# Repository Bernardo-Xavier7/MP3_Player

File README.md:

# Description
Just a simple MP3 player project. Features a built-in microphone, Wifi and Bluetooth, internal flash and SD card support and two audio ports.

# To-Do
- [ ] Hardware
  - [x] Schematic
    - [x] MCU
    - [x] USB
    - [x] Power
    - [x] Audio
    - [x] Storage
    - [x] Buttons
    - [x] Display
    - [x] Wireless
    - [x] Revision
    - [x] BOM
    - [x] Footprint Assignment
  - [ ] PCB
    - [x] Layout
    - [x] Routing
    - [x] Revision
  - [ ] Firmware
    - [ ] Menu
      - [ ] Buttons
      - [ ] Display
    - [ ] USB Handling
    - [ ] Power Measuring and Display
    - [ ] Play Audio
    - [ ] Record
    - [ ] SD Card File System and Mass Storage
    - [ ] Wireless Conectivity
    - [ ] Revision
  - [ ] Case
    - [ ] Model
    - [ ] Test
    - [ ] Revision
# Useful Links
| Link | Description |
| ---- | ---- |
| https://snapeda.com | Symbols/Footprints/3DModels |
| https://octopart.com | Multi-seller component browser |
| https://buydisplay.com | Display shop |
| https://panelook.com | Display shop |
| [https://dev.st.com](https://dev.st.com/stm32cube-docs/stm32cube-getting-started/1.1.1/en/markup/Ecosystem_Select/Ecosystem_Select_MCU_Board.html) | STM32 development guide |

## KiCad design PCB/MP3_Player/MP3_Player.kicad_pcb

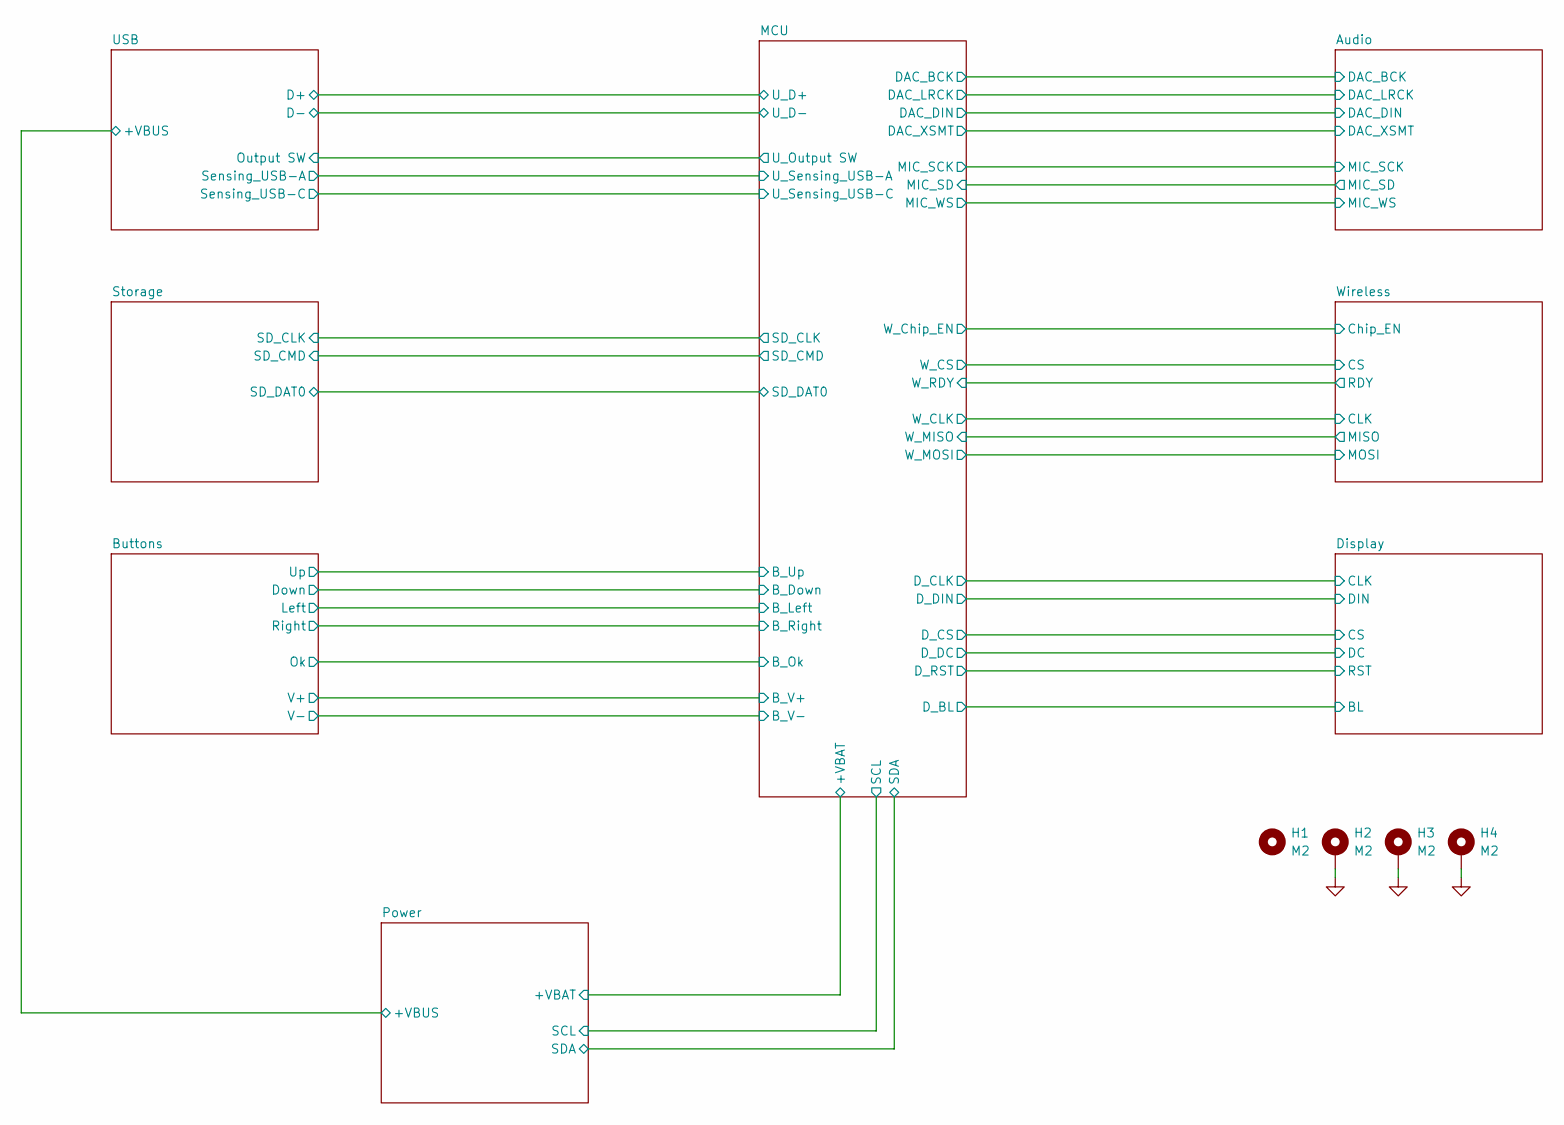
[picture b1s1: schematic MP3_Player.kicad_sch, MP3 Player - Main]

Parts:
H1: M2; MountingHole_2.2mm_M2
H2, H3, H4: M2; MountingHole_2.2mm_M2_DIN965_Pad_TopBottom

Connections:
GND: H2.1 (1_1), H3.1 (1_1), H4.1 (1_1); also elsewhere on the board

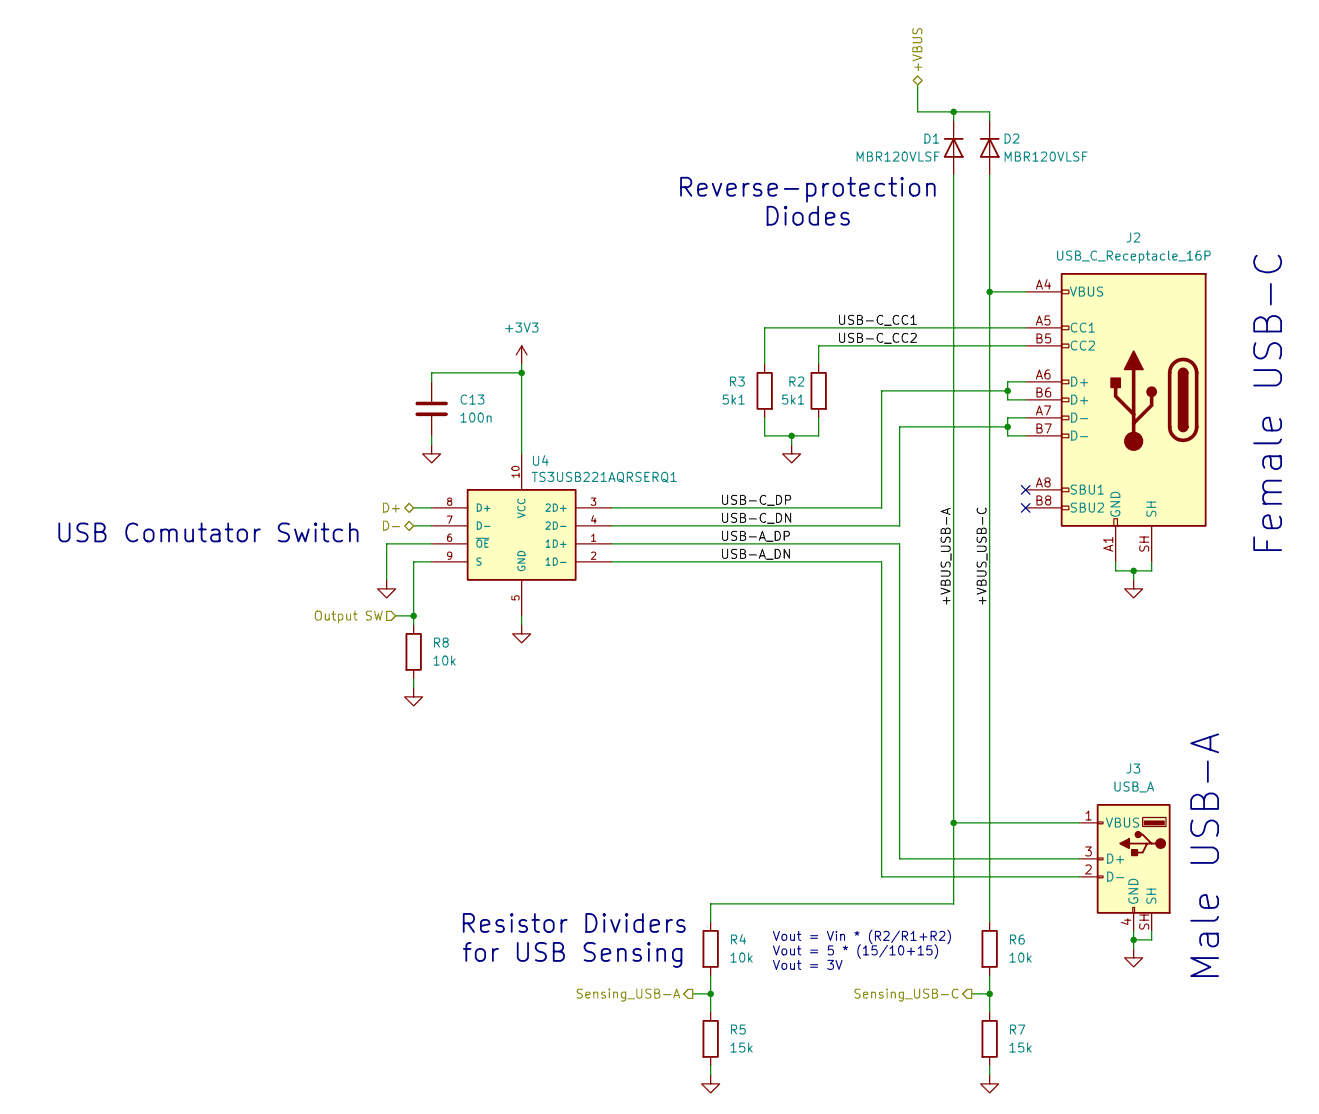
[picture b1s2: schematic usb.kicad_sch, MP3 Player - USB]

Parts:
C13: 100n; C_0402_1005Metric; Mfr. Part # CL05B104KP5NNNC
D1, D2: MBR120VLSF; D_SOD-123F; Mfr. Part # MBR120VLSFT3G
J2: USB_C_Receptacle_16P; USB_C_Receptacle_G-Switch_GT-USB-7010ASV; Mfr. Part # UJ20-C-H-C-4-SMT-TR
J3: USB_A; USB_A_CNCTech_1001-011-01101_Horizontal; Mfr. Part # 931
R2, R3: 5k1; R_0402_1005Metric; Mfr. Part # CRCW04025K10FKED
R4, R6, R8: 10k; R_0402_1005Metric; Mfr. Part # CRCW040210K0FKED
R5, R7: 15k; R_0402_1005Metric; Mfr. Part # CRCW040215K0FKED
U4: TS3USB221AQRSERQ1; MOUSER_PART_NUMBER 595-S3USB221AQRSERQ1

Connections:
+3V3: C13.1, U4.10 (VCC); also elsewhere on the board
/MCU/U_D+: U4.8 (D+); also elsewhere on the board
/MCU/U_D-: U4.7 (D-); also elsewhere on the board
/MCU/U_Output SW: R8.1, U4.9 (S); also elsewhere on the board
/MCU/U_Sensing_USB-A: R4.2, R5.1; also elsewhere on the board
/MCU/U_Sensing_USB-C: R6.2, R7.1; also elsewhere on the board
/Power/+VBUS: D1.1 (K), D2.1 (K); also elsewhere on the board
/USB/+VBUS_USB-A: D1.2 (A), J3.1 (VBUS), R4.1
/USB/+VBUS_USB-C: D2.2 (A), J2.A4 (VBUS), J2.A9 (VBUS), J2.B4 (VBUS), J2.B9 (VBUS), R6.1
/USB/USB-A_DN: J3.2 (D-), U4.2 (1D-)
/USB/USB-A_DP: J3.3 (D+), U4.1 (1D+)
/USB/USB-C_CC1: J2.A5 (CC1), R3.1
/USB/USB-C_CC2: J2.B5 (CC2), R2.1
/USB/USB-C_DN: J2.A7 (D-), J2.B7 (D-), U4.4 (2D-)
/USB/USB-C_DP: J2.A6 (D+), J2.B6 (D+), U4.3 (2D+)
GND: C13.2, J2.A1 (GND), J2.A12 (GND), J2.B1 (GND), J2.B12 (GND), J2.SH, J3.4 (GND), J3.SH, R2.2, R3.2, R5.2, R7.2, R8.2, U4.5 (GND), U4.6 (~OE); also elsewhere on the board

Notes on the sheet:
Vout = Vin * (R2/R1+R2) Vout = 5 * (15/10+15) Vout = 3V
Reverse-protection Diodes
USB Comutator Switch
Male USB-A
Resistor Dividers for USB Sensing
Female USB-C

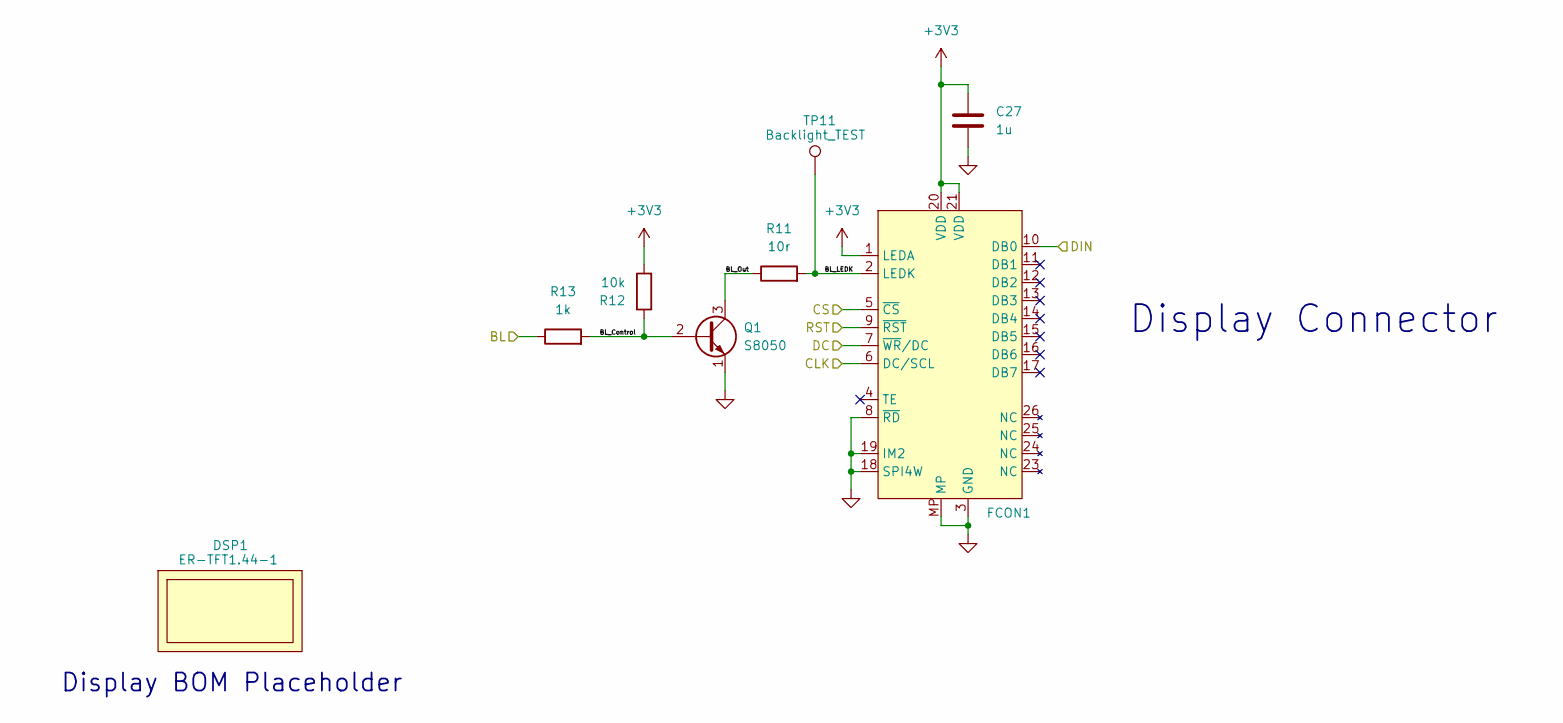
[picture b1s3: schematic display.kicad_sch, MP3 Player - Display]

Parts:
C27: 1u; C_0402_1005Metric; Mfr. Part # CL05A105MQ5NNND
DSP1: ER-TFT1.44-1; N/A; Mfr. Part # ER-TFT1.44-1
FCON1: 26 Pins 0.5mm; Amphenol_F32R-1A7x1-11026_1x26-1MP_P0.5mm_Horizontal
Q1: S8050; TSOT-23; Mfr. Part # S8050
R11: 10r; R_0603_1608Metric; Mfr. Part # CRCW060310R0FKEA
R12: 10k; R_0402_1005Metric; Mfr. Part # CRCW040210K0FKED
R13: 1k; R_0402_1005Metric; Mfr. Part # CRCW04021K00FKED
TP11: Backlight_TEST; TestPoint_Pad_D1.0mm

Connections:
+3V3: C27.1, FCON1.1 (LEDA), FCON1.20 (VDD), FCON1.21 (VDD), R12.2; also elsewhere on the board
/Display/BL: R13.1; also elsewhere on the board
/Display/BL_Control: Q1.2 (B), R12.1, R13.2
/Display/BL_LEDK: FCON1.2 (LEDK), R11.2, TP11.1 (1_1)
/Display/BL_Out: Q1.3 (C), R11.1
/Display/CLK: FCON1.6 (DC/SCL); also elsewhere on the board
/Display/CS: FCON1.5 (~CS); also elsewhere on the board
/Display/DC: FCON1.7 (~WR/DC); also elsewhere on the board
/Display/DIN: FCON1.10 (DB0); also elsewhere on the board
/Display/RST: FCON1.9 (~RST); also elsewhere on the board
GND: C27.2, FCON1.3 (GND), FCON1.8 (~RD), FCON1.18 (SPI4W), FCON1.19 (IM2), FCON1.22 (GND), FCON1.MP, Q1.1 (E); also elsewhere on the board

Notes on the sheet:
Display BOM Placeholder
Display Connector

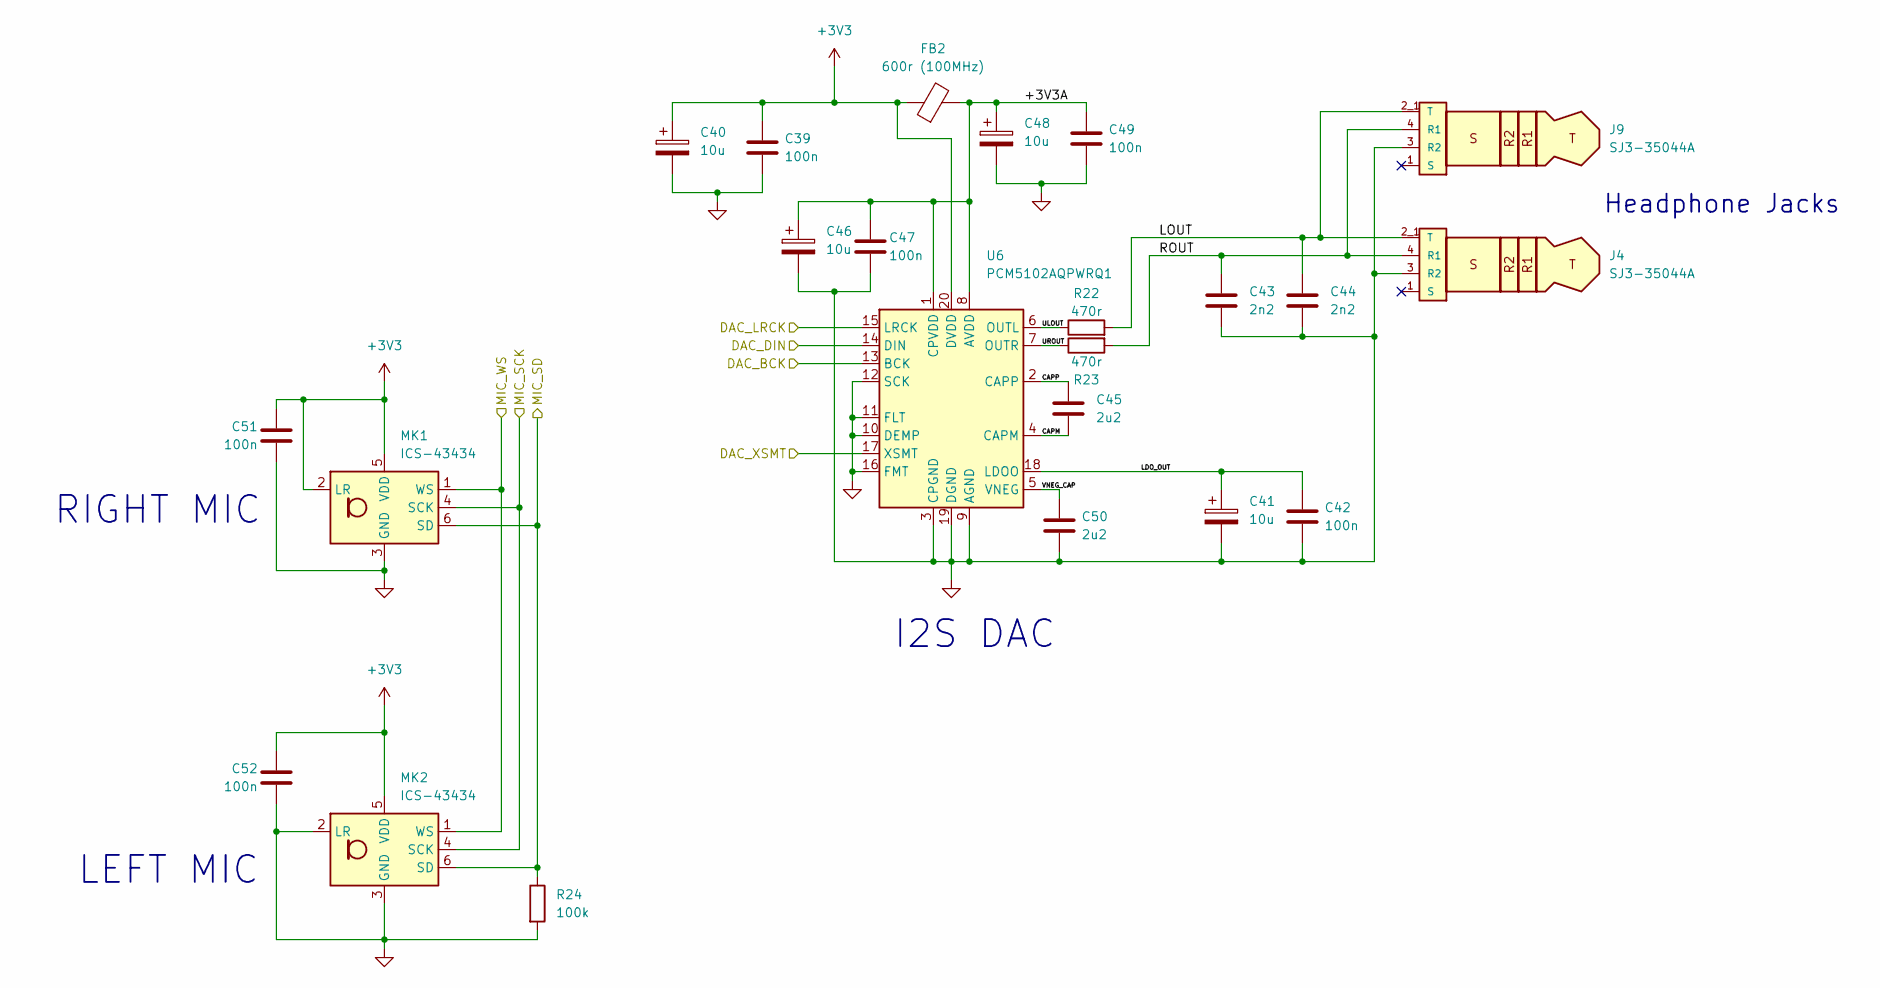
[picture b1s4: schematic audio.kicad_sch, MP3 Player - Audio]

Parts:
C39, C42, C47, C49, C51, C52: 100n; C_0402_1005Metric; Mfr. Part # CL05B104KP5NNNC
C40, C41, C46, C48: 10u; CP_EIA-2012-15_AVX-P; Mfr. Part # T529P106M010AAE200
C43, C44: 2n2; C_0402_1005Metric; Mfr. Part # CL05B222JB5NNNC
C45, C50: 2u2; C_0402_1005Metric; Mfr. Part # CL05A225MQ5NNND
FB2: 600r (100MHz); C_0402_1005Metric; Mfr. Part # BLM15AG601SN1D
J4, J9: SJ3-35044A; SAMESKY_SJ3-35044A; PARTREV 1.0
MK1, MK2: ICS-43434; InvenSense_ICS-43434-6_3.5x2.65mm; Mfr. Part # ICS-43434
R22, R23: 470r; R_0603_1608Metric; Mfr. Part # CRCW0603470RFKEA
R24: 100k; R_0402_1005Metric; Mfr. Part # CRCW0402100KFKED
U6: PCM5102AQPWRQ1; TSSOP-20_4.4x6.5mm_P0.65mm; Mfr. Part # PCM5102AQPWRQ1

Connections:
+3V3: C39.1, C40.1, C51.1, C52.1, FB2.1, MK1.2 (LR), MK1.5 (VDD), MK2.5 (VDD), U6.20 (DVDD); also elsewhere on the board
/Audio/+3V3A: C46.1, C47.1, C48.1, C49.1, FB2.2, U6.1 (CPVDD), U6.8 (AVDD)
/Audio/CAPM: C45.2, U6.4 (CAPM)
/Audio/CAPP: C45.1, U6.2 (CAPP)
/Audio/DAC_BCK: U6.13 (BCK); also elsewhere on the board
/Audio/DAC_DIN: U6.14 (DIN); also elsewhere on the board
/Audio/DAC_LRCK: U6.15 (LRCK); also elsewhere on the board
/Audio/DAC_XSMT: U6.17 (XSMT); also elsewhere on the board
/Audio/LDO_OUT: C41.1, C42.1, U6.18 (LDOO)
/Audio/LOUT: C44.1, J4.2_1 (T), J4.2_2, J9.2_1 (T), J9.2_2, R22.2
/Audio/MIC_SCK: MK1.4 (SCK), MK2.4 (SCK); also elsewhere on the board
/Audio/MIC_SD: MK1.6 (SD), MK2.6 (SD), R24.1; also elsewhere on the board
/Audio/MIC_WS: MK1.1 (WS), MK2.1 (WS); also elsewhere on the board
/Audio/ROUT: C43.1, J4.4 (R1), J9.4 (R1), R23.2
/Audio/ULOUT: R22.1, U6.6 (OUTL)
/Audio/UROUT: R23.1, U6.7 (OUTR)
/Audio/VNEG_CAP: C50.1, U6.5 (VNEG)
GND: C39.2, C40.2, C41.2, C42.2, C43.2, C44.2, C46.2, C47.2, C48.2, C49.2, C50.2, C51.2, C52.2, J4.3 (R2), J9.3 (R2), MK1.3 (GND), MK2.2 (LR), MK2.3 (GND), R24.2, U6.3 (CPGND), U6.9 (AGND), U6.10 (DEMP), U6.11 (FLT), U6.12 (SCK), U6.16 (FMT), U6.19 (DGND); also elsewhere on the board

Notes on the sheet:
Headphone Jacks
LEFT MIC
I2S DAC
RIGHT MIC

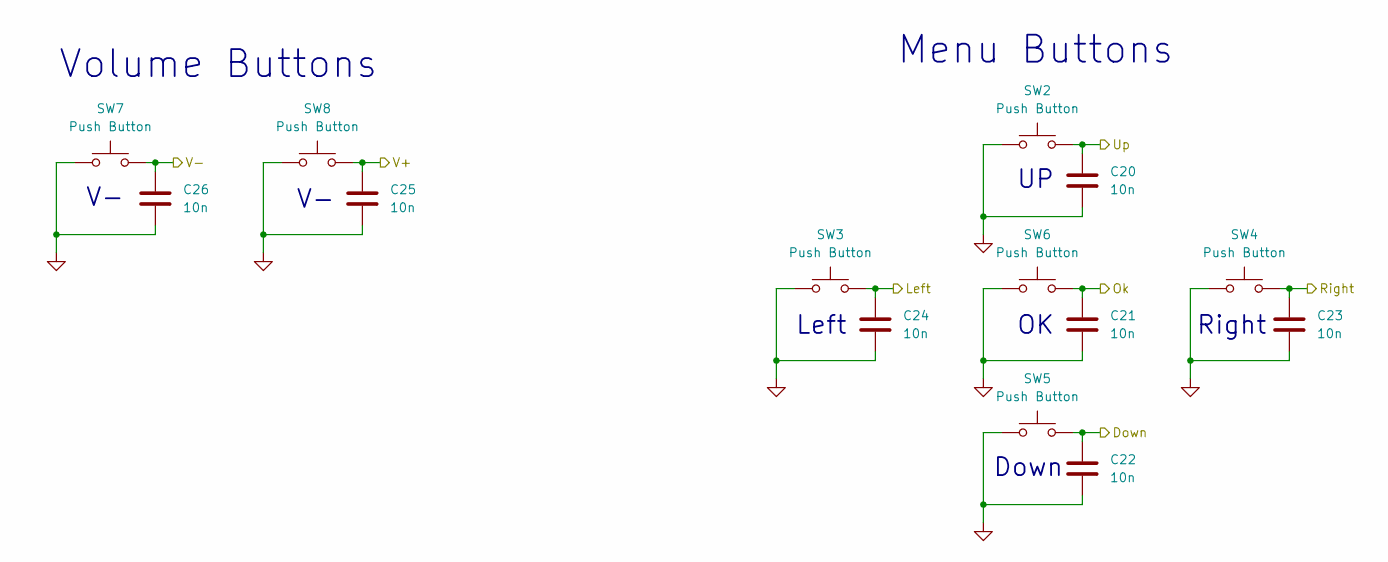
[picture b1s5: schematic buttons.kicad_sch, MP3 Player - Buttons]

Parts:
C20, C21, C22, C23, C24, C25, C26: 10n; C_0402_1005Metric; Mfr. Part # CL05B103KB5NNND
SW2, SW3, SW4, SW5, SW6, SW7, SW8: Push Button; SW_Push_SPST_NO_Alps_SKRK; Mfr. Part # TL1017ABAF260QG

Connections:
/Buttons/Down: C22.1, SW5.1; also elsewhere on the board
/Buttons/Left: C24.1, SW3.2; also elsewhere on the board
/Buttons/Ok: C21.1, SW6.2; also elsewhere on the board
/Buttons/Right: C23.1, SW4.1; also elsewhere on the board
/Buttons/Up: C20.1, SW2.2; also elsewhere on the board
/Buttons/V+: C25.1, SW8.1; also elsewhere on the board
/Buttons/V-: C26.1, SW7.2; also elsewhere on the board
GND: C20.2, C21.2, C22.2, C23.2, C24.2, C25.2, C26.2, SW2.1, SW3.1, SW4.2, SW5.2, SW6.1, SW7.1, SW8.2; also elsewhere on the board

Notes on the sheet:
Right
Down
Menu Buttons
Left
Volume Buttons

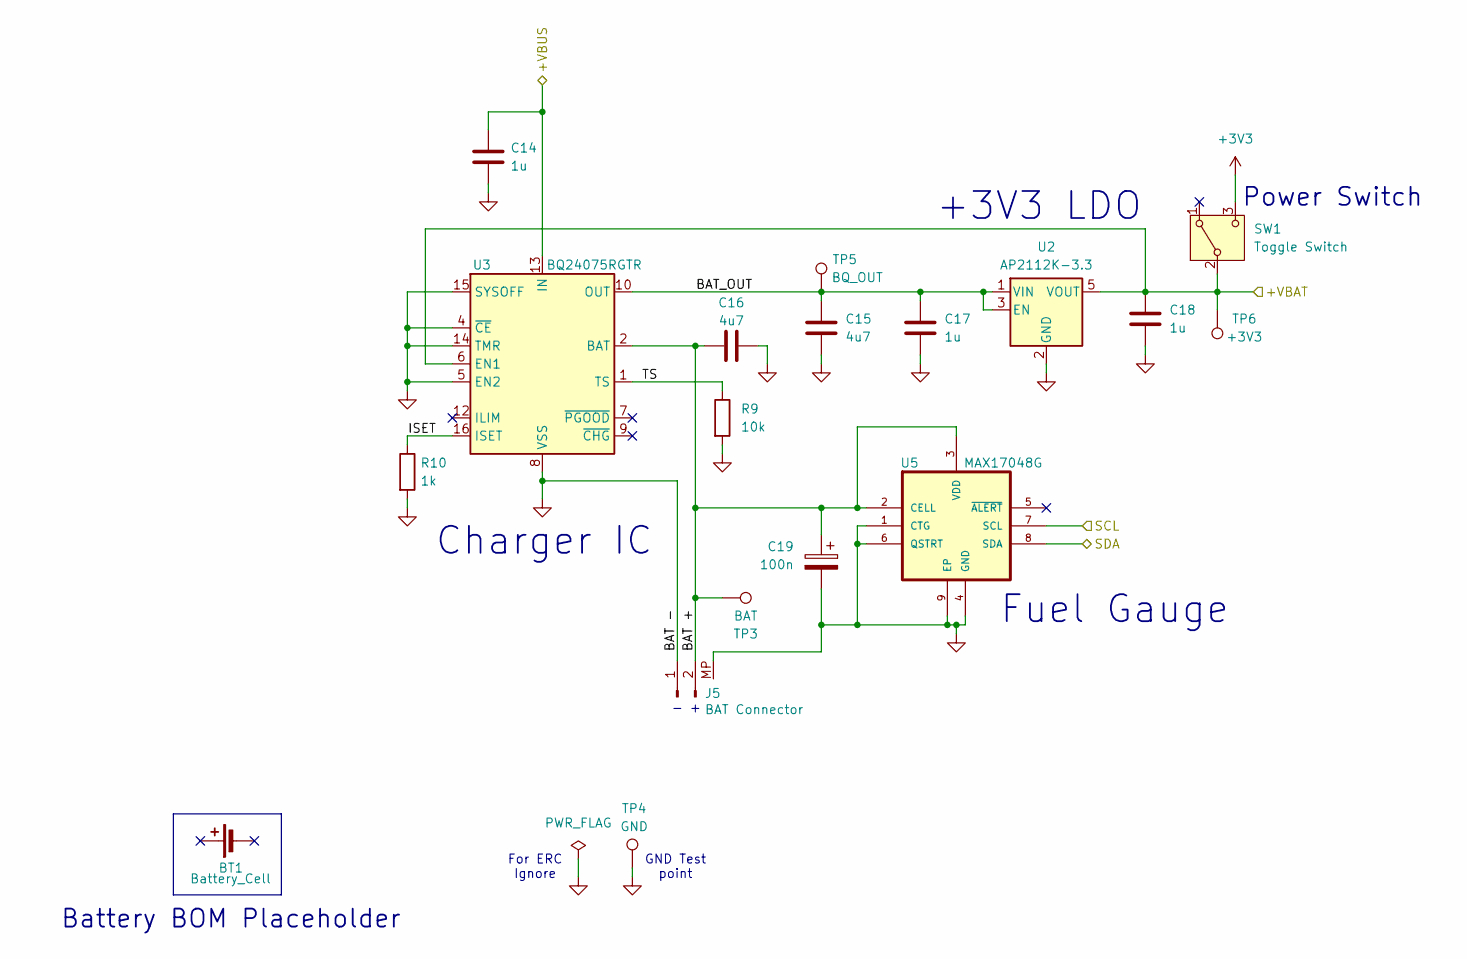
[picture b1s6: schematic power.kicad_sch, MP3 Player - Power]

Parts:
BT1: Battery_Cell; N/A
C14, C17, C18: 1u; C_0402_1005Metric; Mfr. Part # CL05A105MQ5NNND
C15, C16: 4u7; C_0603_1608Metric; Mfr. Part # CL10A475KQ8NNNL
C19: 100n; C_0402_1005Metric; Mfr. Part # CL05B104KP5NNNC
J5: BAT Connector; JST_PH_S2B-PH-SM4-TB_1x02-1MP_P2.00mm_Horizontal; Mfr. Part # S2B-PH-SM4-TB
R9: 10k; R_0402_1005Metric; Mfr. Part # CRCW040210K0FKED
R10: 1k; R_0402_1005Metric; Mfr. Part # CRCW04021K00FKED
SW1: Toggle Switch; SW_SPDT_CK_JS102011SAQN; Mfr. Part # SWS010-020R12SSA
TP3: BAT; TestPoint_Pad_D1.0mm
TP4: GND; TestPoint_Pad_D1.0mm
TP5: BQ_OUT; TestPoint_Pad_D1.0mm
TP6: +3V3; TestPoint_Pad_D1.0mm
U2: AP2112K-3.3; SOT-23-5; Mfr. Part # AP2112K-3.3TRG1
U3: BQ24075RGTR; VQFN-16-1EP_3x3mm_P0.5mm_EP1.6x1.6mm; Mfr. Part # BQ24075RGTR
U5: MAX17048G; SON50P200X200X80-9N; Mfr. Part # MAX17048G+T10

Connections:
+3V3: SW1.3 (C); also elsewhere on the board
/MCU/+VBAT: C18.1, SW1.2 (B), TP6.1 (1_1), U2.5 (VOUT), U3.6 (EN1); also elsewhere on the board
/MCU/SCL: U5.7 (SCL); also elsewhere on the board
/MCU/SDA: U5.8 (SDA); also elsewhere on the board
/Power/+VBUS: C14.1, U3.13 (IN); also elsewhere on the board
/Power/BAT +: C16.1, C19.1, J5.2, TP3.1 (1_1), U3.2 (BAT), U3.3 (BAT), U5.2 (CELL), U5.3 (VDD)
/Power/BAT_OUT: C15.1, C17.1, TP5.1 (1_1), U2.1 (VIN), U2.3 (EN), U3.10 (OUT), U3.11 (OUT)
/Power/ISET: R10.1, U3.16 (ISET)
/Power/TS: R9.1, U3.1 (TS)
GND: C14.2, C15.2, C16.2, C17.2, C18.2, C19.2, J5.1, J5.MP, R9.2, R10.2, TP4.1 (1_1), U2.2 (GND), U3.4 (~CE), U3.5 (EN2), U3.8 (VSS), U3.14 (TMR), U3.15 (SYSOFF), U3.17 (VSS), U5.1 (CTG), U5.4 (GND), U5.6 (QSTRT), U5.9 (EP); also elsewhere on the board

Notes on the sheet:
Charger IC
Battery BOM Placeholder
+3V3 LDO
- +
For ERC Ignore
Fuel Gauge
GND Test point
Power Switch

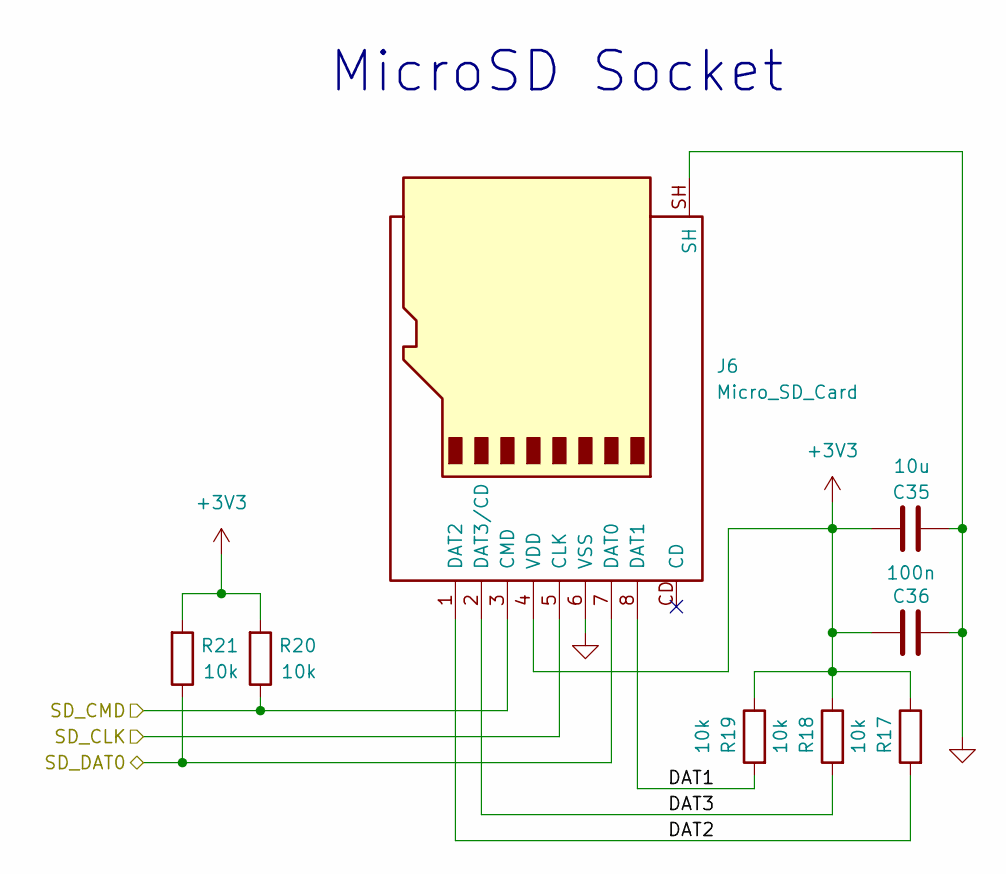
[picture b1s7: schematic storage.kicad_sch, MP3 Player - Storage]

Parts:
C35: 10u; C_0603_1608Metric; Mfr. Part # CL10A106KP8NNNC
C36: 100n; C_0402_1005Metric; Mfr. Part # CL05B104KP5NNNC
J6: Micro_SD_Card; CUI_MSD-1-A; Mfr. Part # MSD-1-A
R17, R18, R19, R20, R21: 10k; R_0402_1005Metric; Mfr. Part # CRCW040210K0FKED

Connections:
+3V3: C35.1, C36.1, J6.4 (VDD), R17.1, R18.1, R19.1, R20.2, R21.2; also elsewhere on the board
/MCU/SD_CLK: J6.5 (CLK); also elsewhere on the board
/MCU/SD_CMD: J6.3 (CMD), R20.1; also elsewhere on the board
/MCU/SD_DAT0: J6.7 (DAT0), R21.1; also elsewhere on the board
/Storage/DAT1: J6.8 (DAT1), R19.2
/Storage/DAT2: J6.1 (DAT2), R17.2
/Storage/DAT3: J6.2 (DAT3/CD), R18.2
GND: C35.2, C36.2, J6.6 (VSS), J6.SH; also elsewhere on the board

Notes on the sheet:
MicroSD Socket

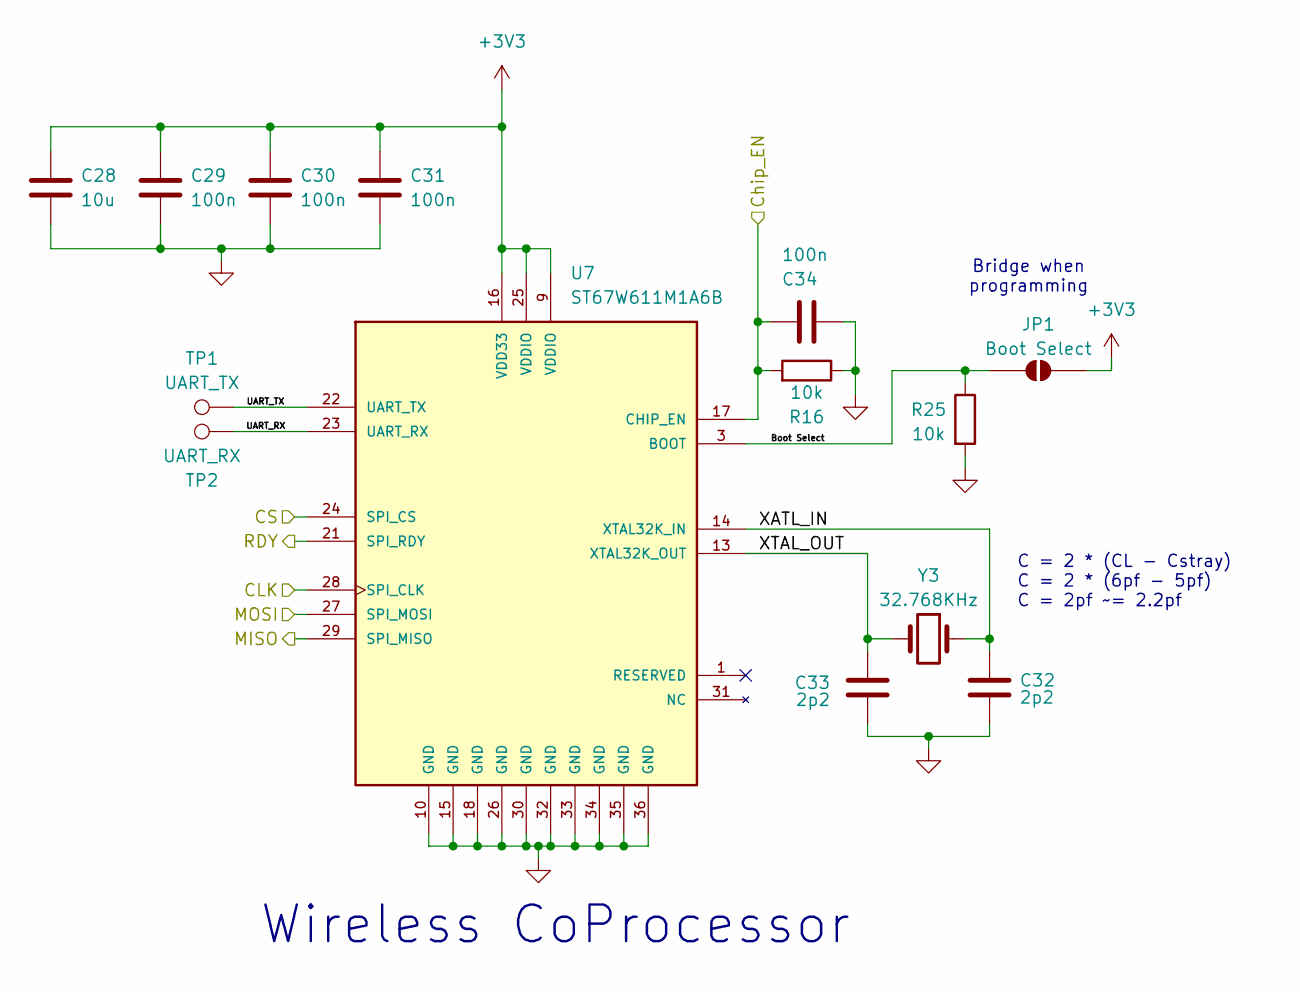
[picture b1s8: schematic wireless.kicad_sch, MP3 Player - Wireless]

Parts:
C28: 10u; C_0603_1608Metric; Mfr. Part # CL10A106KP8NNNC
C29, C30, C31, C34: 100n; C_0402_1005Metric; Mfr. Part # CL05B104KP5NNNC
C32, C33: 2p2; C_0402_1005Metric; Mfr. Part # CL05C2R2CB51PNC
JP1: Boot Select; SolderJumper-2_P1.3mm_Bridged2Bar_RoundedPad1.0x1.5mm
R16, R25: 10k; R_0402_1005Metric; Mfr. Part # CRCW040210K0FKED
TP1: UART_TX; TestPoint_Pad_D1.0mm
TP2: UART_RX; TestPoint_Pad_D1.0mm
U7: ST67W611M1A6B; MODULE_ST67W611M1A6BTR; PARTREV 4
Y3: 32.768KHz; Crystal_SMD_2012-2Pin_2.0x1.2mm; Mfr. Part # FC2012SN

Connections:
+3V3: C28.1, C29.1, C30.1, C31.1, JP1.2 (B), U7.9 (VDDIO), U7.16 (VDD33), U7.25 (VDDIO); also elsewhere on the board
/MCU/W_CLK: U7.28 (SPI_CLK); also elsewhere on the board
/MCU/W_CS: U7.24 (SPI_CS); also elsewhere on the board
/MCU/W_Chip_EN: C34.2, R16.2, U7.17 (CHIP_EN); also elsewhere on the board
/MCU/W_MISO: U7.29 (SPI_MISO); also elsewhere on the board
/MCU/W_MOSI: U7.27 (SPI_MOSI); also elsewhere on the board
/MCU/W_RDY: U7.21 (SPI_RDY); also elsewhere on the board
/Wireless/Boot Select: JP1.1 (A), R25.1, U7.3 (BOOT)
/Wireless/UART_RX: TP2.1 (1_1), U7.23 (UART_RX)
/Wireless/UART_TX: TP1.1 (1_1), U7.22 (UART_TX)
/Wireless/XATL_IN: C32.1, U7.14 (XTAL32K_IN), Y3.1
/Wireless/XTAL_OUT: C33.1, U7.13 (XTAL32K_OUT), Y3.2
GND: C28.2, C29.2, C30.2, C31.2, C32.2, C33.2, C34.1, R16.1, R25.2, U7.10 (GND), U7.15 (GND), U7.18 (GND), U7.26 (GND), U7.30 (GND), U7.32 (GND), U7.33 (GND), U7.34 (GND), U7.35 (GND), U7.36 (GND); also elsewhere on the board

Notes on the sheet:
Wireless CoProcessor
C = 2 * (CL - Cstray) C = 2 * (6pf - 5pf) C = 2pf ~= 2.2pf
Bridge when programming

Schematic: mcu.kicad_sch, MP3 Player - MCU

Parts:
C1, C2, C3, C4, C6, C37, C38: 100n; C_0402_1005Metric; Mfr. Part # CL05B104KP5NNNC
C5: 10u; C_0603_1608Metric; Mfr. Part # CL10A106KP8NNNC
C7: 1u; C_0402_1005Metric; Mfr. Part # CL05A105MQ5NNND
C8: 4u7 (LowESR < 1Ω); C_0603_1608Metric; Mfr. Part # CL10A475KA8NQNC
C9, C10, C11, C12: 2p2; C_0402_1005Metric; Mfr. Part # CL05C2R2CB51PNC
FB1: 600r (100MHz); C_0402_1005Metric; Mfr. Part # BLM15AG601SN1D
J1: TC2030; Tag-Connect_TC2030-IDC-NL_2x03_P1.27mm_Vertical
JP2: Boot Select; SolderJumper-3_P1.3mm_Bridged12_RoundedPad1.0x1.5mm
JP3: Addr Select; SolderJumper-3_P1.3mm_Bridged12_RoundedPad1.0x1.5mm
R1: 10k; R_0402_1005Metric; Mfr. Part # CRCW040210K0FKED
R14, R15: 4k7; R_0402_1005Metric; Mfr. Part # CRCW04024K70FKED
TP7: HSE; TestPoint_Pad_D1.0mm
TP8: LSE; TestPoint_Pad_D1.0mm
TP9: SCL; TestPoint_Pad_D1.0mm
TP10: SDA; TestPoint_Pad_D1.0mm
U1: STM32F411CEU6; QFN-48-1EP_7x7mm_P0.5mm_EP5.6x5.6mm; Mfr. Part # STM32F411CEU6
U8: PCAL6408ABSHP; VQFN-16-1EP_3x3mm_P0.5mm_EP1.6x1.6mm; Mfr. Part # PCAL6408ABSHP
Y1: 25MHz; Crystal_SMD_2016-4Pin_2.0x1.6mm; Mfr. Part # XRCGB25M000F3L25R0
Y2: 32.768KHz; Crystal_SMD_2012-2Pin_2.0x1.2mm; Mfr. Part # FC2012SN

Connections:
+3V3: C2.1, C3.1, C4.1, C5.1, C37.1, C38.1, FB1.1, J1.1, JP2.1 (A), JP3.3 (B), R14.1, R15.1, U1.24 (VDD), U1.36 (VDD), U1.48 (VDD), U8.1 (~RESET), U8.14 (V_{DD(P)}), U8.15 (V_{DD(I2C)}); also elsewhere on the board
/Audio/DAC_BCK: U1.18 (PB0); also elsewhere on the board
/Audio/DAC_DIN: U1.31 (PA10); also elsewhere on the board
/Audio/DAC_LRCK: U1.19 (PB1); also elsewhere on the board
/Audio/DAC_XSMT: U1.20 (PB2); also elsewhere on the board
/Audio/MIC_SCK: U1.25 (PB12); also elsewhere on the board
/Audio/MIC_SD: U1.41 (PB5); also elsewhere on the board
/Audio/MIC_WS: U1.38 (PA15); also elsewhere on the board
/Buttons/Down: U8.4 (P2); also elsewhere on the board
/Buttons/Left: U8.3 (P1); also elsewhere on the board
/Buttons/Ok: U8.5 (P3); also elsewhere on the board
/Buttons/Right: U8.7 (P4); also elsewhere on the board
/Buttons/Up: U8.2 (P0); also elsewhere on the board
/Buttons/V+: U8.8 (P5); also elsewhere on the board
/Buttons/V-: U8.9 (P6); also elsewhere on the board
/Display/BL: U1.45 (PB8); also elsewhere on the board
/Display/CLK: U1.26 (PB13); also elsewhere on the board
/Display/CS: U1.13 (PA3); also elsewhere on the board
/Display/DC: U1.10 (PA0); also elsewhere on the board
/Display/DIN: U1.11 (PA1); also elsewhere on the board
/Display/RST: U1.12 (PA2); also elsewhere on the board
/MCU/+3V3A: C6.1, C7.1, FB1.2, U1.9 (VDDA)
/MCU/+VBAT: C1.1, U1.1 (VBAT); also elsewhere on the board
/MCU/ADDR_SELECT: JP3.2 (C), U8.16 (ADDR)
/MCU/BOOT0: R1.2, U1.44 (BOOT0)
/MCU/BOOT0R: JP2.2 (C), R1.1
/MCU/HSE_IN: C10.1, U1.5 (PH0), Y1.1
/MCU/HSE_OUT: C9.1, TP7.1 (1_1), U1.6 (PH1), Y1.3
/MCU/LSE_IN: C11.1, U1.3 (PC14), Y2.1
/MCU/LSE_OUT: C12.1, TP8.1 (1_1), U1.4 (PC15), Y2.2
/MCU/MUX_INT: U1.2 (PC13), U8.11 (~INT)
/MCU/NRST: J1.3, U1.7 (NRST)
/MCU/SCL: R14.2, TP9.1 (1_1), U1.42 (PB6), U8.12 (SCL); also elsewhere on the board
/MCU/SDA: R15.2, TP10.1 (1_1), U1.46 (PB9), U8.13 (SDA); also elsewhere on the board
/MCU/SD_CLK: U1.28 (PB15); also elsewhere on the board
/MCU/SD_CMD: U1.16 (PA6); also elsewhere on the board
/MCU/SD_DAT0: U1.43 (PB7); also elsewhere on the board
/MCU/SWCLK: J1.4, U1.37 (PA14)
/MCU/SWDIO: J1.2, U1.34 (PA13)
/MCU/SWO: J1.6, U1.39 (PB3)
/MCU/U_D+: U1.33 (PA12); also elsewhere on the board
/MCU/U_D-: U1.32 (PA11); also elsewhere on the board
/MCU/U_Output SW: U8.10 (P7); also elsewhere on the board
/MCU/U_Sensing_USB-A: U1.30 (PA9); also elsewhere on the board
/MCU/U_Sensing_USB-C: U1.29 (PA8); also elsewhere on the board
/MCU/VCAP: C8.1, U1.22 (VCAP1)
/MCU/W_CLK: U1.15 (PA5); also elsewhere on the board
/MCU/W_CS: U1.14 (PA4); also elsewhere on the board
/MCU/W_Chip_EN: U1.21 (PB10); also elsewhere on the board
/MCU/W_MISO: U1.40 (PB4); also elsewhere on the board
/MCU/W_MOSI: U1.17 (PA7); also elsewhere on the board
/MCU/W_RDY: U1.27 (PB14); also elsewhere on the board
GND: C1.2, C2.2, C3.2, C4.2, C5.2, C6.2, C7.2, C8.2, C9.2, C10.2, C11.2, C12.2, C37.2, C38.2, J1.5, JP2.3 (B), JP3.1 (A), U1.8 (VSSA), U1.23 (VSS), U1.35 (VSS), U1.47 (VSS), U1.49 (VSS), U8.6 (V_{SS}), U8.17 (V_{SS}), Y1.2 (G), Y1.4 (G); also elsewhere on the board

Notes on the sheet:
Enable pull-ups for buttons in frimware
Main MCU
Cut and bridge once MCU firmware is done
Change if it has address conflicts
Boot Set Pins
I2C MUX
C = 2 * (CL - Cstray) C = 2 * (6pf - 5pf) C = 2pf ~= 2.2pf
TagConnect Pins
I2C Test Points

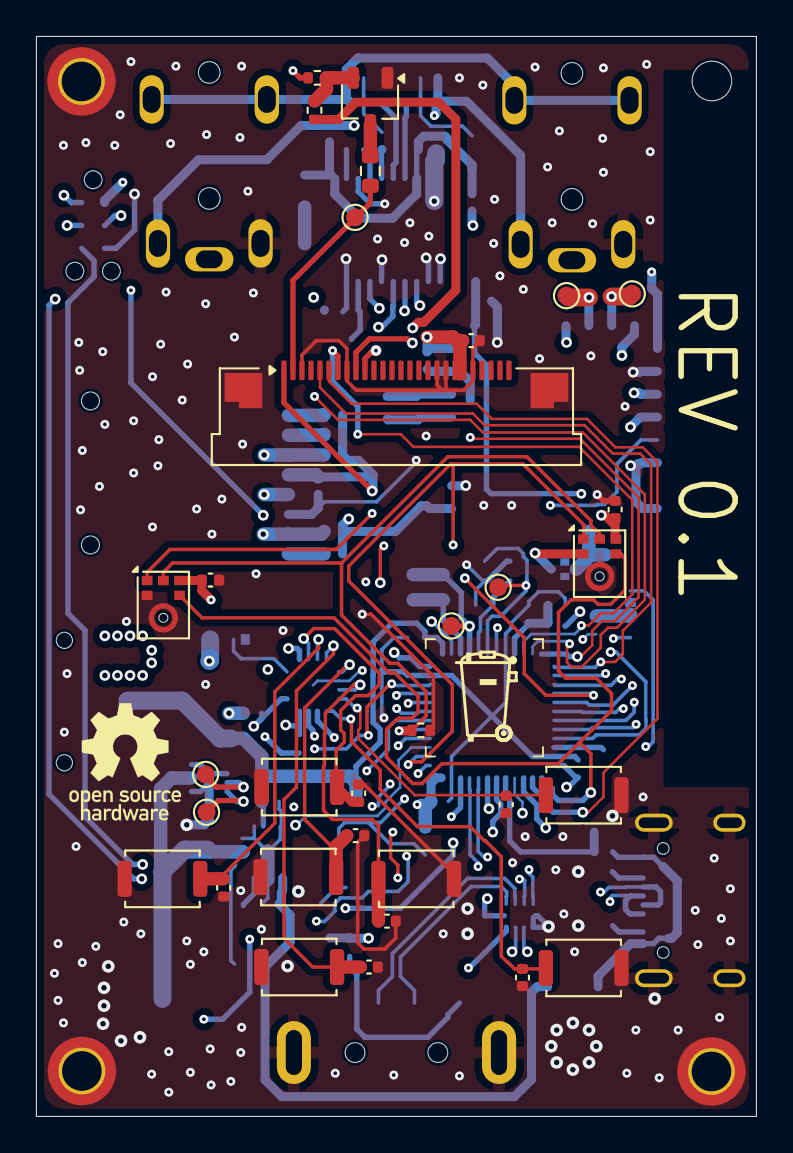
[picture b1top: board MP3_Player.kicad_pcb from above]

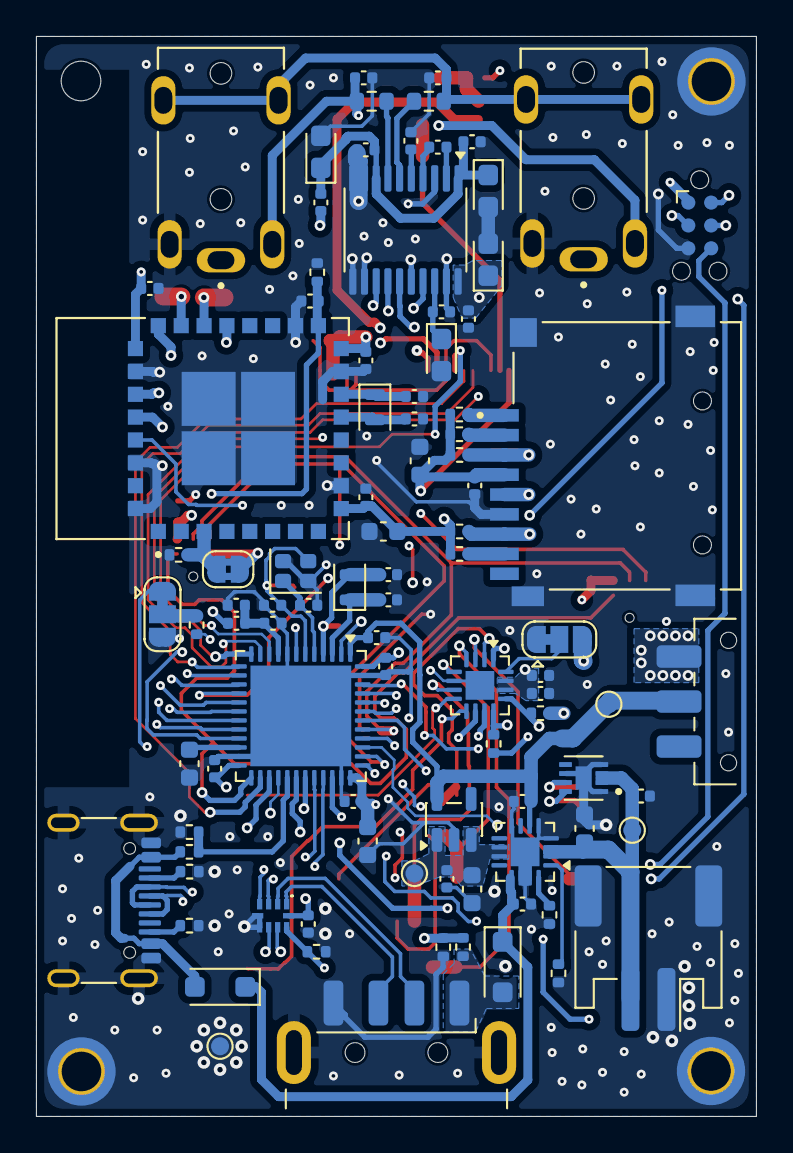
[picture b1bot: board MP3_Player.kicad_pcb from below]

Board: 6 copper layers, 40.0 x 60.0 mm, 129 parts (93 on the bottom side), 86 nets.

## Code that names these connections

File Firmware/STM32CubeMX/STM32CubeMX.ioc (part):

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Mcu.Name=STM32F411C(C-E)Ux
Mcu.Package=UFQFPN48
Mcu.UserName=STM32F411CEUx
PA0-WKUP.GPIOParameters=GPIO_Label
PA0-WKUP.GPIO_Label=D_DC
PA0-WKUP.Signal=GPIO_Output
PA1.Mode=Simplex_Bidirectional_Master
PA1.Signal=SPI4_MOSI
PA10.Mode=Half_Duplex_Master
PA10.Signal=I2S5_SD
PA11.Mode=Device_Only
PA11.Signal=USB_OTG_FS_DM
PA12.Mode=Device_Only
PA12.Signal=USB_OTG_FS_DP
PA13.Mode=Trace_Asynchronous_SW
PA13.Signal=SYS_JTMS-SWDIO
PA14.Mode=Trace_Asynchronous_SW
PA14.Signal=SYS_JTCK-SWCLK
PA15.Mode=Half_Duplex_Master
PA15.Signal=I2S3_WS
PA2.GPIOParameters=GPIO_Label
PA2.GPIO_Label=D_RST
PA2.Signal=GPIO_Output
PA3.GPIOParameters=GPIO_Label
PA3.GPIO_Label=D_CS
PA3.Signal=GPIO_Output
PA4.Mode=NSS_Signal_Hard_Output
PA4.Signal=SPI1_NSS
PA5.Mode=Full_Duplex_Master
PA5.Signal=SPI1_SCK
PA6.Mode=SD_1_bit
PA6.Signal=SDIO_CMD
PA7.Mode=Full_Duplex_Master
PA7.Signal=SPI1_MOSI
PA8.GPIOParameters=GPIO_Label
PA8.GPIO_Label=Sens_USBC
PA8.Signal=GPIO_Input
PA9.GPIOParameters=GPIO_Label
PA9.GPIO_Label=Sens_USBA
PA9.Mode=Activate_VBUS
PA9.Signal=USB_OTG_FS_VBUS
PB0.Mode=Half_Duplex_Master
PB0.Signal=I2S5_CK
PB1.Mode=Half_Duplex_Master
PB1.Signal=I2S5_WS
PB10.GPIOParameters=GPIO_Label
PB10.GPIO_Label=W_ChipEN
PB10.Signal=GPIO_Output
PB12.Mode=Half_Duplex_Master
PB12.Signal=I2S3_CK
PB13.Mode=Simplex_Bidirectional_Master
PB13.Signal=SPI4_SCK
PB14.GPIOParameters=GPIO_Label
PB14.GPIO_Label=W_RDY
PB14.Signal=GPIO_Input
PB15.Mode=SD_1_bit
PB15.Signal=SDIO_CK
PB2.GPIOParameters=GPIO_Label
PB2.GPIO_Label=CODEC_XSMT
PB2.Signal=GPIO_Output
PB3.Mode=Trace_Asynchronous_SW
PB3.Signal=SYS_JTDO-SWO
PB4.Mode=Full_Duplex_Master
PB4.Signal=SPI1_MISO
PB5.Mode=Half_Duplex_Master
PB5.Signal=I2S3_SD
PB6.Mode=I2C
PB6.Signal=I2C1_SCL
PB7.Mode=SD_1_bit
PB7.Signal=SDIO_D0
PB8.Signal=S_TIM10_CH1
PB9.Mode=I2C
PB9.Signal=I2C1_SDA
PC14-OSC32_IN.Mode=LSE-External-Oscillator
PC14-OSC32_IN.Signal=RCC_OSC32_IN
PC15-OSC32_OUT.Mode=LSE-External-Oscillator
PC15-OSC32_OUT.Signal=RCC_OSC32_OUT
PH0\ -\ OSC_IN.Mode=HSE-External-Oscillator
PH0\ -\ OSC_IN.Signal=RCC_OSC_IN
PH1\ -\ OSC_OUT.Mode=HSE-External-Oscillator
PH1\ -\ OSC_OUT.Signal=RCC_OSC_OUT
RCC.HSE_VALUE=25000000
RCC.SYSCLKFreq_VALUE=16000000
board=custom
